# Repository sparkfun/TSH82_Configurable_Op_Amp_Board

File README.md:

SparkFun Configurable OpAmp Board - TSH82
========================================

[*SparkFun Configurable OpAmp Board - TSH82 (14874)*](https://www.sparkfun.com/products/14874)

The SparkFun TSH82 Configurable OpAmp Board was designed to give you the best combination of performance and flexibility that we could achieve by giving you two gain stages, each one independently accessible on the header pins. Each stage is natively configured as an inverting amplifier that can also be strung together to expand the capabilities of the OpAmp. With the use of the jumpers on the back of the board, you can configure each stage for non-inverting operation, differential input, and DC input coupling.

Electrically speaking, both stages on this board are identical. The default configuration is inverting with a gain of -4.7 with a bandwidth of almost 10MHz. Input signals are AC coupled, possess an input impedance of 10K with a low frequency cutoff of 15.9Hz. Outputs are also DC coupled, so don’t forget to add a capacitor to the output if you’re running a single-ended supply and need to strip out the DC component. The board will also operate with a single-ended DC power supply of 4.5V to 12V, or a bipolar supply from +/-2.25V to +/-6V.

On the back of the board you’ll find 10 solder jumpers that can be used to change the board’s performance, but nothing there needs to be changed to use it in it’s default state.

Repository Contents
-------------------
* **/Hardware** - Eagle design files (.brd, .sch)
* **/Production** - Production panel files (.brd)

Documentation
--------------
* **[Hookup Guide](https://learn.sparkfun.com/tutorials/tsh82-configurable-opamp-hookup-guide)** - Basic hookup guide for the SparkFun Configurable OpAmp Board - TSH82.
* **[SparkFun Fritzing repo](https://github.com/sparkfun/Fritzing_Parts)** - Fritzing diagrams for SparkFun products.

License Information
-------------------

This product is _**open source**_! 

Please review the LICENSE.md file for license information. 

If you have any questions or concerns on licensing, please contact techsupport@sparkfun.com.

Distributed as-is; no warranty is given.

- Your friends at SparkFun.

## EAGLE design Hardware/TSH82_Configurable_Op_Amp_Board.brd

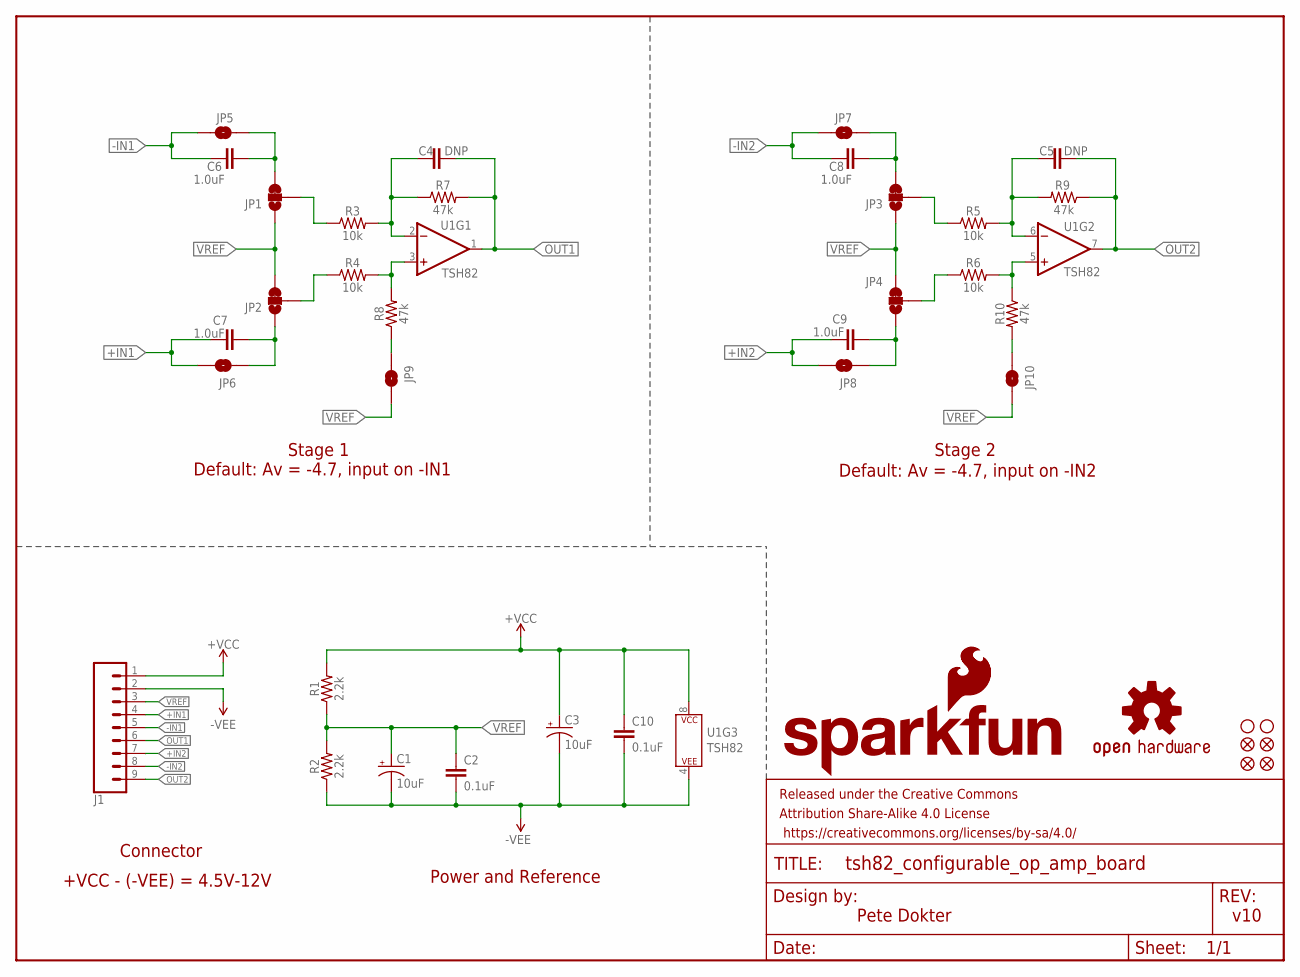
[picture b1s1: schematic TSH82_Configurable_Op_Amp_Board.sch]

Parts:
C1, C3: 10uF; EIA3216
C2, C10: 0.1uF; 0603
C4, C5: DNP; 0603
C6, C7, C8, C9: 1.0uF; 0603
FD1, FD2, FD3, FD4: FIDUCIALUFIDUCIAL; FIDUCIAL-MICRO
FRAME1: FRAME-LETTER; CREATIVE_COMMONS
H1, H2: STAND-OFF
J1: CONN_09NO_SILK; 1X09_NO_SILK
JP1, JP2, JP3, JP4: JUMPER-SMT_3_1-NC_TRACE_SILK; SMT-JUMPER_3_1-NC_TRACE_SILK
JP5, JP6, JP7, JP8, JP9, JP10: JUMPER-SMT_2_NO_SILK; SMT-JUMPER_2_NO_SILK
LOGO1: SFE_LOGO_FLAME.2_INCH; SFE_LOGO_FLAME_.2
LOGO2: SFE_LOGO_NAME_FLAME.1_INCH; SFE_LOGO_NAME_FLAME_.1
LOGO3: OSHW-LOGOS; OSHW-LOGO-S
R1, R2: 2.2k; 0603
R3, R4, R5, R6: 10k; 0603
R7, R8, R9, R10: 47k; 0603
U1: TSH82; SO08

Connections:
+IN1: C7.1, J1.4, JP6.2
+IN2: C9.1, J1.7, JP8.2
-IN1: C6.1, J1.5, JP5.2
-IN2: C8.1, J1.8, JP7.2
unnamed: C4.1, R3.2, R7.1, U1.2 (-IN)
unnamed: R4.2, R8.2, U1.3 (+IN)
unnamed: JP9.1, R8.1
unnamed: JP1.2, R3.1
unnamed: JP2.2, R4.1
unnamed: C6.2, JP1.3, JP5.1
unnamed: C7.2, JP2.1, JP6.1
unnamed: C8.2, JP3.3, JP7.1
unnamed: JP3.2, R5.1
unnamed: C5.1, R5.2, R9.2, U1.6 (-IN)
unnamed: JP4.2, R6.1
unnamed: C9.2, JP4.1, JP8.1
unnamed: R6.2, R10.1, U1.5 (+IN)
unnamed: JP10.1, R10.2
OUT1: C4.2, J1.6, R7.2, U1.1 (OUT)
OUT2: C5.2, J1.9, R9.1, U1.7 (OUT)
VCC: C3.+, C10.1, J1.1, R1.2, U1.8 (P$V+)
VNEG: C1.-, C2.2, C3.-, C10.2, J1.2, R2.1, U1.4 (P$V-)
VREF: C1.+, C2.1, J1.3, JP1.1, JP2.3, JP3.1, JP4.3, JP9.2, JP10.2, R1.1, R2.2

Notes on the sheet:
Stage 1
Default: Av = -4.7, input on -IN1
Default: Av = -4.7, input on -IN2
Stage 2
Pete Dokter
Connector
Power and Reference
v10
+VCC - (-VEE) = 4.5V-12V

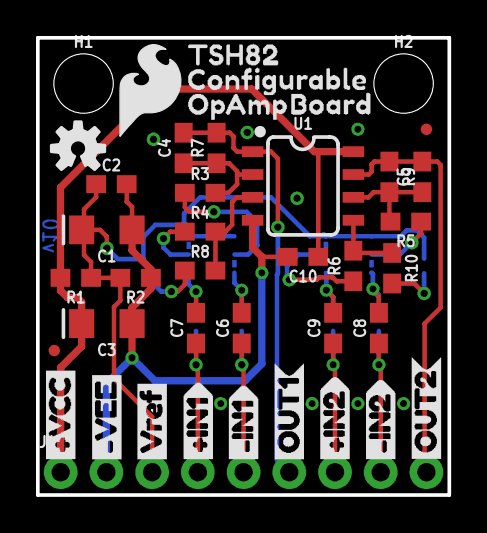
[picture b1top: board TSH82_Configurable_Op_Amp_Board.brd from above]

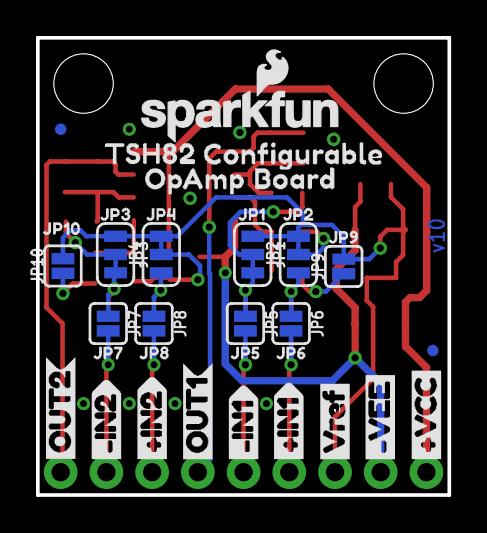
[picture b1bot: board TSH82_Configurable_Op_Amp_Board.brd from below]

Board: 2 copper layers, 22.9 x 25.4 mm, 78 parts (36 on the bottom side), 23 nets.

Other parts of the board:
U$1, U$2: #VEE1
U$3, U$30: #VCC0
U$4, U$5: VREF6
U$6, U$7: #IN12
U$8, U$9: #IN13
U$10, U$11: OUT17
U$12, U$13: #IN24
U$14, U$16: #IN25
U$15, U$17: OUT28
U$18: JP10
U$19: JP21
U$20: JP32
U$21: JP43
U$22, U$26: TSH820
U$23, U$27: CONFIGURABLE1
U$24, U$28: OPAMP2
U$25, U$29: BOARD3
U$31: JP54
U$32: JP65
U$33: JP76
U$34: JP87
U$35: JP98
U$36: JP109

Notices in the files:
parts and their libraries:
SparkFun-Capacitors: Licensing: Creative Commons ShareAlike 4.0 International - https://creativecommons.org/licenses/by-sa/4.0
SparkFun-Aesthetics: Released under the Creative Commons Attribution Share-Alike 4.0 License
SparkFun-Aesthetics: https://creativecommons.org/licenses/by-sa/4.0
